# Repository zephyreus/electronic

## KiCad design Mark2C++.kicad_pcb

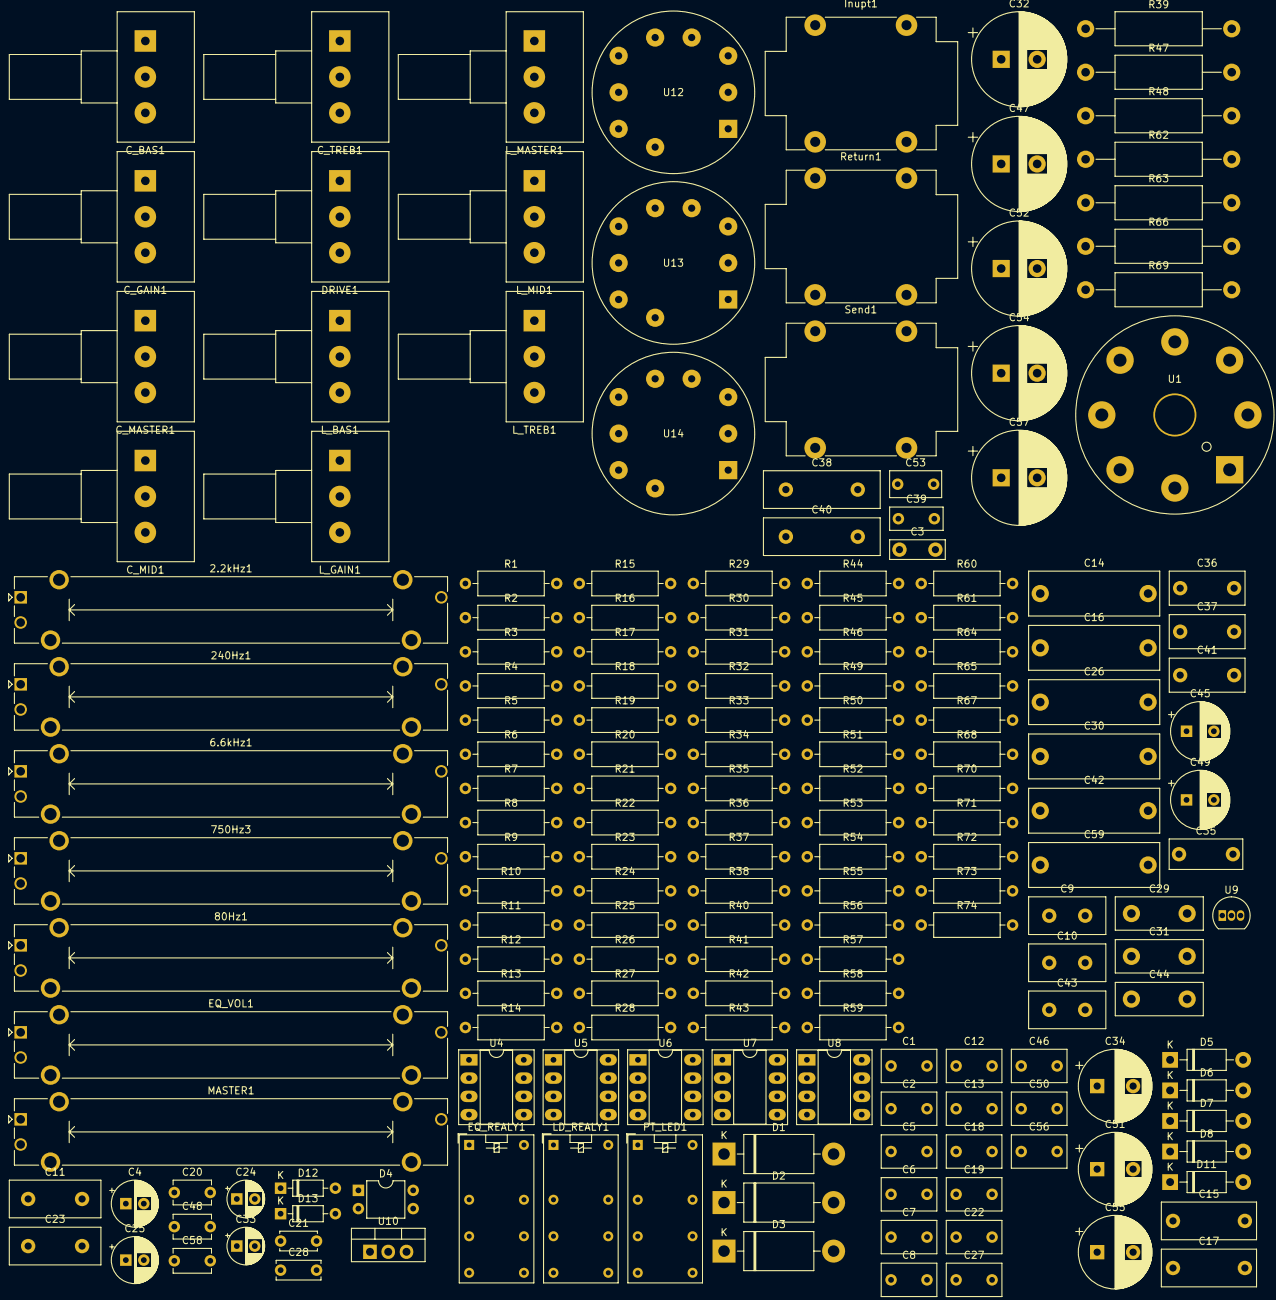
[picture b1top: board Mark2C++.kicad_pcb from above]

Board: 2 copper layers, 179 parts (0 on the bottom side), 107 nets, no tracks yet.

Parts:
2.2kHz1, 6.6kHz1, 80Hz1, 240Hz1, 750Hz3: 50K Lin; Potentiometer_Bourns_PTA4543_Single_Slide
C1, C5: 1uF 50V; C_Disc_D7.5mm_W4.4mm_P5.00mm
C2, C18: 47nF 50V; C_Disc_D7.5mm_W4.4mm_P5.00mm
C3: 470nF 35V; C_Disc_D7.5mm_W2.5mm_P5.00mm
C4, C25: 22uF 35V; CP_Radial_D6.3mm_P2.50mm
C6: 8.2nF 50V; C_Disc_D7.5mm_W4.4mm_P5.00mm
C7, C8, C22, C27, C46, C50: 10nF 50V; C_Disc_D7.5mm_W4.4mm_P5.00mm
C9, C10, C43: 250pF 400V; C_Disc_D10.5mm_W5.0mm_P5.00mm
C11, C23: 680pF 400V; C_Disc_D12.5mm_W5.0mm_P7.50mm
C12: 100nF 50V; C_Disc_D7.5mm_W4.4mm_P5.00mm
C13: 4.7nF 50V; C_Disc_D7.5mm_W4.4mm_P5.00mm
C14, C16, C26, C30, C42: 47nF 400V; C_Rect_L18.0mm_W6.0mm_P15.00mm_FKS3_FKP3
C15, C17: 100nF 400V; C_Rect_L13.0mm_W5.0mm_P10.00mm_FKS3_FKP3_MKS4
C19: 2.2nF 50V; C_Disc_D7.5mm_W4.4mm_P5.00mm
C20: 150pF 50V; C_Disc_D5.1mm_W3.2mm_P5.00mm
C21: 180pF 400V; C_Disc_D5.0mm_W2.5mm_P5.00mm
C24: 1uF/50V; CP_Radial_D5.0mm_P2.50mm
C28: 10pF 400V; C_Disc_D6.0mm_W2.5mm_P5.00mm
C29: 47pF 1kV; C_Disc_D12.0mm_W4.4mm_P7.75mm
C31: 120pF 400V; C_Disc_D12.0mm_W4.4mm_P7.75mm
C32: 22uF 400V; CP_Radial_D13.0mm_P5.00mm
C33: 2.2uF 35V; CP_Radial_D5.0mm_P2.50mm
C34: 47uF 50V; CP_Radial_D10.0mm_P5.00mm
C35: 3.3nF 400V; C_Rect_L10.0mm_W4.0mm_P7.50mm_MKS4
C36, C37, C41: 22nF 400V; C_Rect_L10.3mm_W4.5mm_P7.50mm_MKS4
C38, C40: 1000pF 400V; C_Disc_D16.0mm_W5.0mm_P10.00mm
C39: 220nF 50V; C_Rect_L7.2mm_W3.0mm_P5.00mm_FKS2_FKP2_MKS2_MKP2
C44: 500pF 400V; C_Disc_D12.0mm_W4.4mm_P7.75mm
C45, C49: 220uF 35V; CP_Radial_D8.0mm_P3.80mm
C47, C52, C54, C57: 22uF 450V; CP_Radial_D13.0mm_P5.00mm
C48: 47pF 50V; C_Disc_D5.1mm_W3.2mm_P5.00mm
C51, C55: 100uF 50V; CP_Radial_D10.0mm_P5.00mm
C53: 100nF; C_Rect_L7.0mm_W3.5mm_P5.00mm
C56: 100nF; C_Disc_D7.5mm_W4.4mm_P5.00mm
C58: 100pF 50V; C_Disc_D5.1mm_W3.2mm_P5.00mm
C59: 22nF 400V; C_Rect_L18.0mm_W6.0mm_P15.00mm_FKS3_FKP3
C_BAS1: 250K Log; Potentiometer_Alps_RK163_Single_Horizontal
C_GAIN1: 1M Log; Potentiometer_Alps_RK163_Single_Horizontal
C_MASTER1: 250K Log; Potentiometer_Alps_RK163_Single_Horizontal
C_MID1: 10K Lin; Potentiometer_Alps_RK163_Single_Horizontal
C_TREB1: 250K Log; Potentiometer_Alps_RK163_Single_Horizontal
D1, D2, D3: UF4007; D_DO-201AD_P15.24mm_Horizontal
D4: Bridge; DIP-4_W7.62mm
D5, D6, D7, D8, D11: UF4007; D_DO-41_SOD81_P10.16mm_Horizontal
D12, D13: 1N4148; D_DO-35_SOD27_P7.62mm_Horizontal
DRIVE1: 1M Log; Potentiometer_Alps_RK163_Single_Horizontal
EQ_REALY1: G6SU-2; Relay_DPDT_Omron_G5V-2
EQ_VOL1: 50K Lin; Potentiometer_Bourns_PTA4543_Single_Slide
Inupt1: AudioJack2_Ground_Switch; Jack_6.35mm_Neutrik_NMJ4HCD2_Horizontal
LD_REALY1: G6SU-2; Relay_DPDT_Omron_G5V-2
L_BAS1: 250K Log; Potentiometer_Alps_RK163_Single_Horizontal
L_GAIN1: 1M Log; Potentiometer_Alps_RK163_Single_Horizontal
L_MASTER1: 250K Log; Potentiometer_Alps_RK163_Single_Horizontal
L_MID1: 10K Lin; Potentiometer_Alps_RK163_Single_Horizontal
L_TREB1: 250K Log; Potentiometer_Alps_RK163_Single_Horizontal
MASTER1: 1M Lin; Potentiometer_Bourns_PTA4543_Single_Slide
PT_LED1: G6SU-2; Relay_DPDT_Omron_G5V-2
R1, R11, R12, R20, R24, R28, R31, R35, R50, R54, R65, R71: 100K; R_Axial_DIN0309_L9.0mm_D3.2mm_P12.70mm_Horizontal
R2, R60, R61: 1M; R_Axial_DIN0309_L9.0mm_D3.2mm_P12.70mm_Horizontal
R3, R27, R34, R40, R49: 1.5K; R_Axial_DIN0309_L9.0mm_D3.2mm_P12.70mm_Horizontal
R4, R16, R26: 820; R_Axial_DIN0309_L9.0mm_D3.2mm_P12.70mm_Horizontal
R5, R41: 150K; R_Axial_DIN0309_L9.0mm_D3.2mm_P12.70mm_Horizontal
R6, R51: 15K; R_Axial_DIN0309_L9.0mm_D3.2mm_P12.70mm_Horizontal
R7, R14: 120K; R_Axial_DIN0309_L9.0mm_D3.2mm_P12.70mm_Horizontal
R8: 2.2M; R_Axial_DIN0309_L9.0mm_D3.2mm_P12.70mm_Horizontal
R9, R23: 470; R_Axial_DIN0309_L9.0mm_D3.2mm_P12.70mm_Horizontal
R10, R64, R70: 1K; R_Axial_DIN0309_L9.0mm_D3.2mm_P12.70mm_Horizontal
R13, R37, R46, R58: 470K; R_Axial_DIN0309_L9.0mm_D3.2mm_P12.70mm_Horizontal
R15, R17, R18, R25, R29, R30, R72: 10K; R_Axial_DIN0309_L9.0mm_D3.2mm_P12.70mm_Horizontal
R19: 10M; R_Axial_DIN0309_L9.0mm_D3.2mm_P12.70mm_Horizontal
R21, R22: 100K (o); R_Axial_DIN0309_L9.0mm_D3.2mm_P12.70mm_Horizontal
R32: 3.3M; R_Axial_DIN0309_L9.0mm_D3.2mm_P12.70mm_Horizontal
R33, R36: 680K; R_Axial_DIN0309_L9.0mm_D3.2mm_P12.70mm_Horizontal
R38, R67, R68: 47K; R_Axial_DIN0309_L9.0mm_D3.2mm_P12.70mm_Horizontal
R39: 470R 2W; R_Axial_DIN0414_L11.9mm_D4.5mm_P20.32mm_Horizontal
R42: 82K; R_Axial_DIN0309_L9.0mm_D3.2mm_P12.70mm_Horizontal
R43: 4.7K; R_Axial_DIN0309_L9.0mm_D3.2mm_P12.70mm_Horizontal
R44, R52: 270K; R_Axial_DIN0309_L9.0mm_D3.2mm_P12.70mm_Horizontal
R45, R59: 68K; R_Axial_DIN0309_L9.0mm_D3.2mm_P12.70mm_Horizontal
R47: 470R 1W; R_Axial_DIN0414_L11.9mm_D4.5mm_P20.32mm_Horizontal
R48: 5,6K 1W; R_Axial_DIN0414_L11.9mm_D4.5mm_P20.32mm_Horizontal
R53: 3.3K; R_Axial_DIN0309_L9.0mm_D3.2mm_P12.70mm_Horizontal
R55: 220K; R_Axial_DIN0309_L9.0mm_D3.2mm_P12.70mm_Horizontal
R56, R57: 100R; R_Axial_DIN0309_L9.0mm_D3.2mm_P12.70mm_Horizontal
R62: 180K 2W; R_Axial_DIN0414_L11.9mm_D4.5mm_P20.32mm_Horizontal
R63: 560R 2W; R_Axial_DIN0414_L11.9mm_D4.5mm_P20.32mm_Horizontal
R66, R69: 2.2K 2W; R_Axial_DIN0414_L11.9mm_D4.5mm_P20.32mm_Horizontal
R73: 12K; R_Axial_DIN0309_L9.0mm_D3.2mm_P12.70mm_Horizontal
R74: 4,7K; R_Axial_DIN0309_L9.0mm_D3.2mm_P12.70mm_Horizontal
Return1: AudioJack2_Ground_Switch; Jack_6.35mm_Neutrik_NMJ4HCD2_Horizontal
Send1: AudioJack2_Ground_Switch; Jack_6.35mm_Neutrik_NMJ4HCD2_Horizontal
U1: EL34; Valve_Octal
U4, U5, U6, U7, U8: NE5532; DIP-8_W7.62mm_Socket_LongPads
U9: LR8; TO-92_Inline
U10: L7812; TO-220-3_Vertical
U12, U13, U14: 6N2P-EW; Valve_Noval_P

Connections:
+6V: C8.1, C55.1, R1.1, R7.1, R13.1, R14.1, R15.2, R20.1, R24.2, R67.2, R68.1, R72.2, U4.3 (+)
+12V: C49.1, C51.1, C53.1, D12.1 (K), R67.1, R74.1, U4.8 (V+), U5.8 (V+), U6.8 (V+), U7.8 (V+), U8.8 (V+), U10.3 (OUT)
GND: C3.2, C20.1, C25.2, C27.2, C29.2, C32.2, C33.2, C34.2, C38.2, C44.1, C45.2, C47.2, C49.2, C51.2, C52.2, C53.2, C54.2, C55.2, C57.2, C_GAIN1.1, C_MASTER1.2, C_MASTER1.3, C_MID1.1, D4.2 (-), D5.2 (A), D6.2 (A), D13.2 (A), DRIVE1.1, EQ_VOL1.1, Inupt1.S, Inupt1.SN, Inupt1.TN, L_GAIN1.1, L_MASTER1.2, L_MASTER1.3, L_MID1.1, MASTER1.1, R2.2, R3.2, R6.2, R8.2, R27.2, R30.2, R31.2, R33.2, R34.2, R37.1, R40.2, R43.1, R45.2, R47.2, R50.2, R51.2, R53.2, R54.2, R59.1, R62.2, R65.1, R68.2, R71.1, Return1.S, Return1.SN, Send1.S, Send1.SN, U4.4 (V-), U5.4 (V-), U6.4 (V-), U7.4 (V-), U8.4 (V-), U10.2 (GND), U12.9 (F2), U13.9 (F2), U14.9 (F2)
unnamed: 2.2kHz1.2, C18.1
unnamed: 6.6kHz1.2, C22.1
unnamed: 80Hz1.2, C1.1
unnamed: 240Hz1.2, C5.1
unnamed: D5.1 (K), D7.2 (A)
unnamed: D6.1 (K), D8.2 (A)
unnamed: C57.1, R69.2
unnamed: C54.1, R66.2, R69.1
unnamed: C52.1, D11.2 (A), R58.1, R63.1, R66.1, U9.2 (OUT)
unnamed: 750Hz3.2, C12.1
unnamed: C_GAIN1.3, R21.2
unnamed: C39.2, R51.1
unnamed: C3.1, C4.1, R3.1, U12.8 (K)
unnamed: C1.2, C2.1, R4.1
unnamed: C4.2, R6.1
unnamed: C5.2, C6.2, R9.1
unnamed: C8.2, R10.2
unnamed: C9.1, C_TREB1.3
unnamed: C12.2, C13.2, R16.1
unnamed: C14.1, C_BAS1.1, C_MID1.2, C_MID1.3
unnamed: C14.2, C15.2, R11.2
unnamed: C15.1, C_BAS1.2, C_BAS1.3, C_TREB1.1
unnamed: C16.1, L_BAS1.1, L_MID1.2, L_MID1.3
unnamed: C16.2, C17.2, R12.2
unnamed: C17.1, L_BAS1.2, L_BAS1.3, L_TREB1.1
unnamed: C18.2, C19.2, R23.1
unnamed: C22.2, C23.2, R26.1
unnamed: C24.1, R25.1, U5.7
unnamed: C24.2, R29.2
unnamed: C26.1, C28.2, C59.2, R31.1, R32.2
unnamed: C27.1, EQ_VOL1.3, R29.1, R30.1
unnamed: C30.1, R38.2
unnamed: C36.1, R44.1
unnamed: C37.2, R41.1, R43.2
unnamed: C42.1, C43.2, R55.1
unnamed: C46.2, R60.2
unnamed: C48.1, C50.1, R61.1, U4.1
unnamed: C50.2, R64.1, R65.2
unnamed: C56.2, R70.1
unnamed: C_TREB1.2, R21.1
unnamed: D1.1 (K), EQ_REALY1.1
unnamed: D2.1 (K), LD_REALY1.1
unnamed: D3.1 (K), PT_LED1.1
unnamed: C45.1, D4.1 (+), U10.1 (IN)
unnamed: C47.1, D7.1 (K), D8.1 (K), D11.1 (K), U9.1 (IN)
unnamed: C56.1, D12.2 (A), D13.1 (K), R71.2, U4.5 (+)
unnamed: DRIVE1.3, R36.1
unnamed: R5.2, U12.6 (A)
unnamed: C9.2, R11.1
unnamed: C21.1, C_GAIN1.2
unnamed: C10.2, C11.2, R12.1
unnamed: C7.1, R8.1
unnamed: C58.1, R73.2, U4.7
unnamed: C28.1, C29.1, R32.1, R33.1, U14.7 (G)
unnamed: C43.1, C44.2, R54.1, R55.2
unnamed: L_GAIN1.3, R22.2
unnamed: L_TREB1.2, R22.1
unnamed: R38.1, R41.2
unnamed: R17.1, R18.2, U5.1
unnamed: R46.1, R49.2, R50.1
unnamed: R56.1, R57.1, R58.2, R59.2
unnamed: R64.2, Return1.TN, Send1.T
unnamed: R70.2, Return1.T
unnamed: C32.1, C35.1, R39.1, R48.1
unnamed: C35.2, U1.3 (A)
unnamed: C11.1, R19.1
unnamed: C10.1, L_TREB1.3, R19.2
unnamed: C34.1, R47.1, U1.8 (F1)
unnamed: MASTER1.2, U1.5 (G1)
unnamed: R48.2, U1.4 (G2)
unnamed: C48.2, R60.1, R61.2, U4.2 (-)
unnamed: C58.2, R72.1, R73.1, U4.6 (-)
unnamed: C7.2, R13.2, U5.3 (+)
unnamed: R10.1, R15.1, R17.2, U5.2 (-)
unnamed: 2.2kHz1.1, 6.6kHz1.1, 80Hz1.1, 240Hz1.1, 750Hz3.1, C20.2, R18.1, U5.5 (+)
unnamed: 2.2kHz1.3, 6.6kHz1.3, 80Hz1.3, 240Hz1.3, 750Hz3.3, R25.2, U5.6 (-)
unnamed: C2.2, R1.2, U6.3 (+)
unnamed: R4.2, U6.1, U6.2 (-)
unnamed: C6.1, R7.2, U6.5 (+)
unnamed: R9.2, U6.6 (-), U6.7
unnamed: C13.1, R14.2, U7.3 (+)
unnamed: R16.2, U7.1, U7.2 (-)
unnamed: C19.1, R20.2, U7.5 (+)
unnamed: R23.2, U7.6 (-), U7.7
unnamed: C23.1, R24.1, U8.3 (+)
unnamed: R26.2, U8.1, U8.2 (-)
unnamed: U8.6 (-), U8.7
unnamed: R62.1, R63.2, U9.3 (ADJ)
unnamed: Inupt1.T, R2.1, U12.7 (G)
unnamed: C26.2, R28.2, U12.1 (A)
unnamed: C25.1, R27.1, U12.3 (K)
unnamed: C36.2, R42.2, U13.6 (A)
unnamed: C31.2, DRIVE1.2, R37.2, U13.7 (G)
unnamed: C31.1, C33.1, R40.1, U13.8 (K)
unnamed: C40.2, C42.2, R52.2, U13.1 (A)
unnamed: C38.1, R44.2, R45.1, U13.2 (G)
unnamed: C39.1, R53.1, U13.3 (K)
unnamed: C30.2, R35.2, U14.6 (A)
unnamed: R34.1, U14.8 (K)
unnamed: C37.1, R46.2, U14.2 (G)
unnamed: C41.2, R49.1, U14.3 (K)
VAA: R5.1, R28.1, R39.2
VCC: R35.1, U14.1 (A)
VDD: C40.1, R42.1, R52.1

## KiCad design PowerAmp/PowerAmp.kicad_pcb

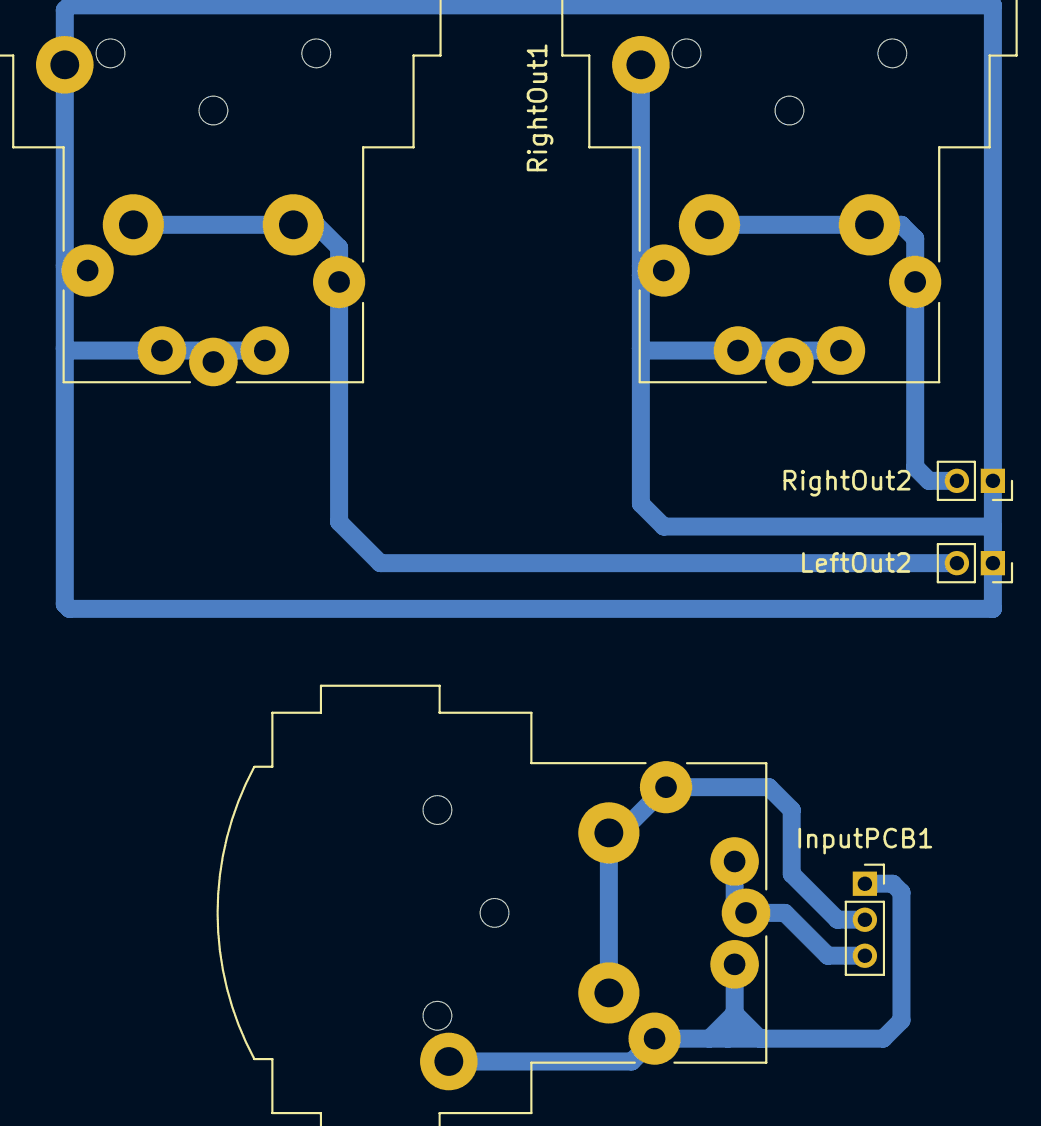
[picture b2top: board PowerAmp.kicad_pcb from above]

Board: 2 copper layers, 6 parts (0 on the bottom side), 6 nets.

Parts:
Input1: XLR3_AudioJack3_Combo_Ground_Switch; Jack_XLR-6.35mm_Neutrik_NCJ6FA-H-0_Horizontal
InputPCB1: Screw_Terminal_01x03; PinSocket_1x03_P2.00mm_Vertical
LeftOut1: XLR3_AudioJack3_Combo_Ground_Switch; Jack_XLR-6.35mm_Neutrik_NCJ6FA-H-0_Horizontal
LeftOut2: Screw_Terminal_01x02; PinSocket_1x02_P2.00mm_Vertical
RightOut1: XLR3_AudioJack3_Combo_Ground_Switch; Jack_XLR-6.35mm_Neutrik_NCJ6FA-H-0_Horizontal
RightOut2: Screw_Terminal_01x02; PinSocket_1x02_P2.00mm_Vertical

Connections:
unnamed: Input1.1, Input1.G, Input1.S, InputPCB1.1
unnamed: Input1.2, Input1.T, InputPCB1.2
unnamed: Input1.3, Input1.R, InputPCB1.3
unnamed: LeftOut1.1, LeftOut1.3, LeftOut1.G, LeftOut1.R, LeftOut1.S, LeftOut2.1, RightOut1.1, RightOut1.3, RightOut1.G, RightOut1.R, RightOut1.S, RightOut2.1
unnamed: LeftOut1.2, LeftOut1.T, LeftOut2.2
unnamed: RightOut1.2, RightOut1.T, RightOut2.2

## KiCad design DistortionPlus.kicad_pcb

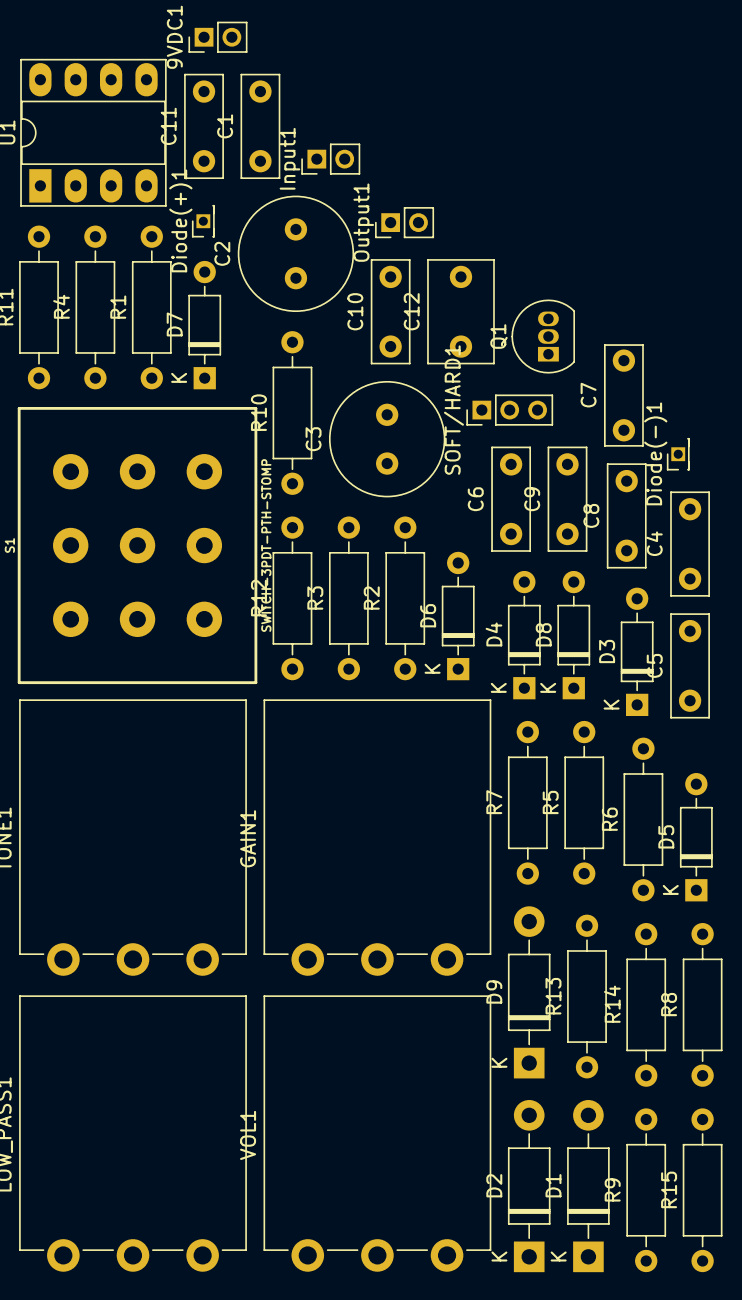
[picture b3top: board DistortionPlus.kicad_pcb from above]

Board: 2 copper layers, 49 parts (0 on the bottom side), 32 nets, no tracks yet.

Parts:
9VDC1: Conn_01x02_Female; PinHeader_1x02_P2.00mm_Vertical
C1: 10nF; C_Rect_L7.2mm_W2.5mm_P5.00mm_FKS2_FKP2_MKS2_MKP2
C2, C3: 220uF; C_Radial_D8.0mm_H7.0mm_P3.50mm
C4, C6, C8: 100nF; C_Rect_L7.2mm_W2.5mm_P5.00mm_FKS2_FKP2_MKS2_MKP2
C5: 150nF; C_Rect_L7.2mm_W2.5mm_P5.00mm_FKS2_FKP2_MKS2_MKP2
C7: 100pF; C_Disc_D7.0mm_W2.5mm_P5.00mm
C9: 6,8nF; C_Rect_L7.2mm_W2.5mm_P5.00mm_FKS2_FKP2_MKS2_MKP2
C10: 4,7nF; C_Rect_L7.2mm_W2.5mm_P5.00mm_FKS2_FKP2_MKS2_MKP2
C11: 2,7nF; C_Rect_L7.2mm_W2.5mm_P5.00mm_FKS2_FKP2_MKS2_MKP2
C12: 470nF; C_Rect_L7.2mm_W4.5mm_P5.00mm_FKS2_FKP2_MKS2_MKP2
D1, D2, D9: 1N4007; D_DO-41_SOD81_P10.16mm_Horizontal
D3, D4, D5, D6, D7, D8: 1N4148; D_DO-35_SOD27_P7.62mm_Horizontal
Diode(+)1: Conn_01x01_Female; PinHeader_1x01_P1.27mm_Vertical
Diode(-)1: Conn_01x01_Female; PinHeader_1x01_P1.27mm_Vertical
GAIN1: 1M LOG; Potentiometer_Piher_PC-16_Single_Vertical
Input1: Conn_01x02_Female; PinHeader_1x02_P2.00mm_Vertical
LOW_PASS1: 5K LIN; Potentiometer_Piher_PC-16_Single_Vertical
Output1: Conn_01x02_Female; PinHeader_1x02_P2.00mm_Vertical
Q1: BC546; TO-92_Inline
R1: 1K; R_Axial_DIN0207_L6.3mm_D2.5mm_P10.16mm_Horizontal
R2, R9: 560K; R_Axial_DIN0207_L6.3mm_D2.5mm_P10.16mm_Horizontal
R3, R4, R11: 4,7K; R_Axial_DIN0207_L6.3mm_D2.5mm_P10.16mm_Horizontal
R5, R12, R13, R15: 10K; R_Axial_DIN0207_L6.3mm_D2.5mm_P10.16mm_Horizontal
R6, R7, R8: 39K; R_Axial_DIN0207_L6.3mm_D2.5mm_P10.16mm_Horizontal
R10: 6,8K; R_Axial_DIN0207_L6.3mm_D2.5mm_P10.16mm_Horizontal
R14: 2K; R_Axial_DIN0207_L6.3mm_D2.5mm_P10.16mm_Horizontal
S1: SWITCH-3PDT-PTH-STOMP; STOMP_SWITCH_3PDT
SOFT/HARD1: SW_SPDT; PinHeader_1x03_P2.00mm_Vertical
TONE1: 50K LIN; Potentiometer_Piher_PC-16_Single_Vertical
U1: TL072; DIP-8_W7.62mm_Socket_LongPads
VOL1: 50K LOG; Potentiometer_Piher_PC-16_Single_Vertical

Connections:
GND: 9VDC1.1, C3.2, C8.1, C9.1, C10.1, D2.2, Input1.1, Output1.1, R4.1, R5.1, R9.1, S1.P$8, U1.4, VOL1.1
unnamed: 9VDC1.2, D9.2
unnamed: C1.1, D1.2, D2.1, Q1.2, R2.2
unnamed: C1.2, R1.1
unnamed: C4.1, R6.2, R7.1
unnamed: C4.2, Q1.3, R5.2
unnamed: C5.1, LOW_PASS1.3
unnamed: C6.1, R9.2
unnamed: C6.2, R7.2, U1.3
unnamed: C7.1, D5.1, D6.2, GAIN1.2, GAIN1.3, R11.1, U1.1
unnamed: C7.2, D3.2, D4.1, LOW_PASS1.1, LOW_PASS1.2, R8.1, U1.2
unnamed: C9.2, R11.2, SOFT/HARD1.2, TONE1.3
unnamed: C10.2, TONE1.1
unnamed: C11.1, R12.2, R13.1, U1.6
unnamed: C11.2, C12.2, R13.2, U1.7
unnamed: C12.1, VOL1.3
unnamed: D3.1, D5.2
unnamed: D4.2, D6.1
unnamed: D7.1, D8.2, SOFT/HARD1.1
unnamed: Diode(+)1.1, R14.2
unnamed: Diode(-)1.1, S1.P$7
unnamed: GAIN1.1, R8.2
unnamed: Input1.2, S1.P$2
unnamed: Output1.2, S1.P$5
unnamed: R1.2, R15.1, S1.P$1
unnamed: R10.1, SOFT/HARD1.3
unnamed: R15.2, S1.P$9
unnamed: S1.P$3, S1.P$6
unnamed: S1.P$4, VOL1.2
unnamed: TONE1.2, U1.5
VB: C2.2, C3.1, C5.2, C8.2, D7.2, D8.1, R2.1, R3.1, R4.2, R6.1, R10.2, R12.1
VCC: C2.1, D1.1, D9.1, Q1.1, R3.2, R14.1, U1.8

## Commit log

2023-08-03 small changes
    - Poprawki w okolicach sekcji Lead
    - Poprawiona nazwa wartości post EQ
2023-08-04 changes in schema and pcb
    updated schemaitc and pcb
